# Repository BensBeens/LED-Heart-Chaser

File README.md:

# LED-Heart-Chaser
Little project that I made as a gift for others. It is a LED chaser circuit that would turn on LEDs in a heart shape when plugged into a USB port. 
It uses a NE555 timer and a 4017 counter for the chaser circuit. It is a 4 layer board (signal layers 1 and 4, VCC layer 3, and GND layer 2)
Hand soldered the SMD components on the PCB when I got the board from Oshpark.com (sourced the components from Mouser.com).

Here is the schematic:

Here is the front of the PCB:

Here is the back of the PCB:

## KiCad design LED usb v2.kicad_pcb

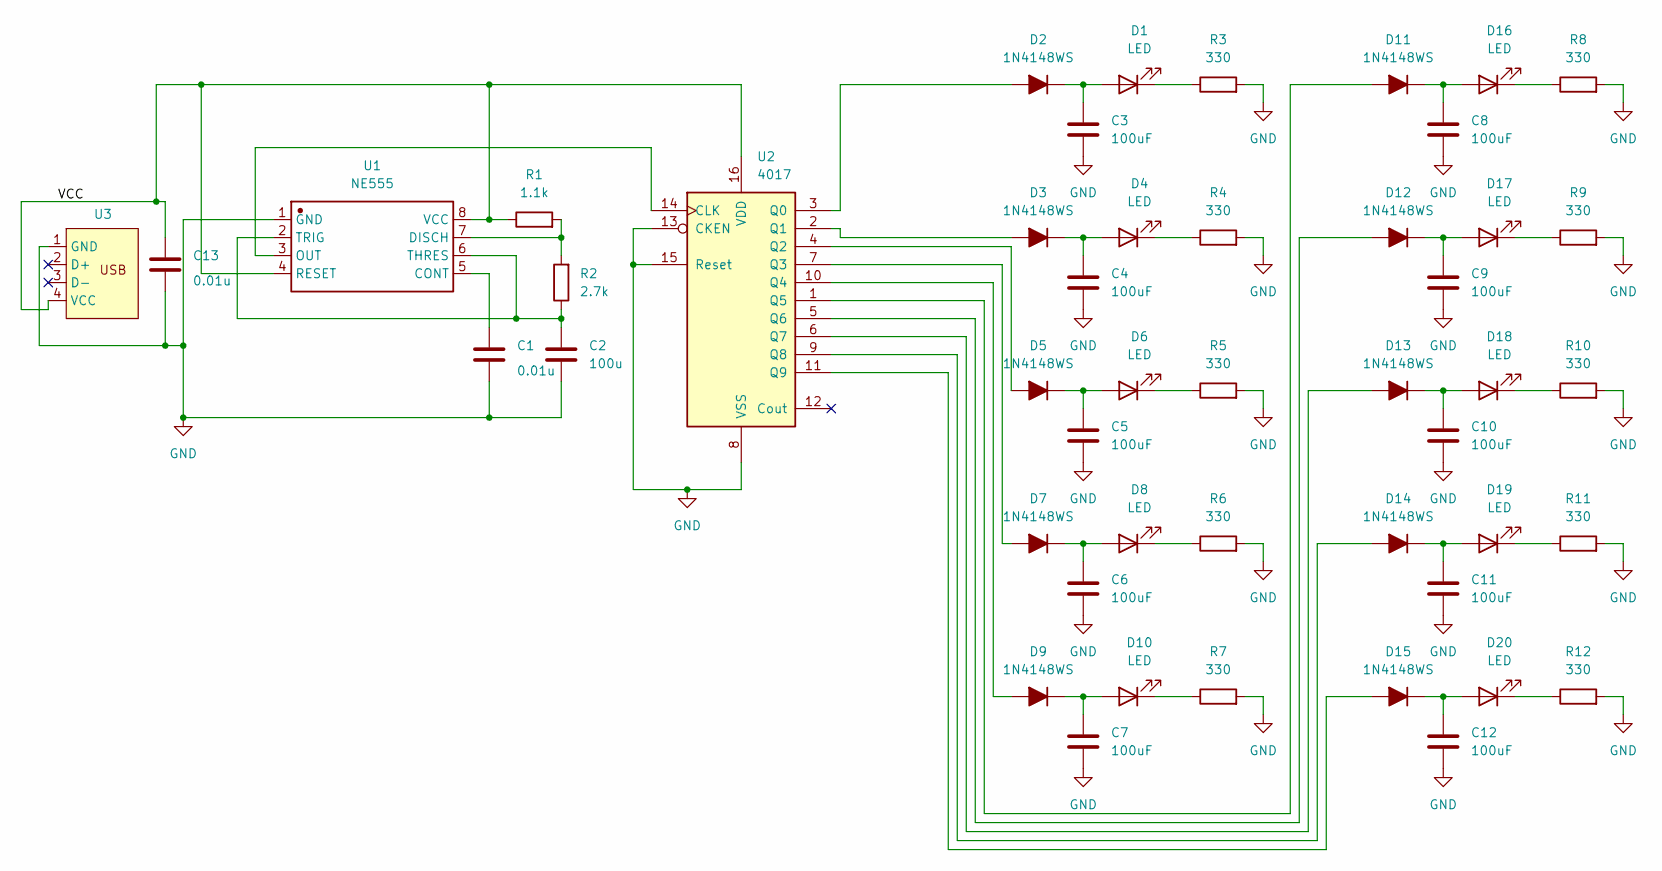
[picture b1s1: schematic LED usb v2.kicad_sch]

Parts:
C1, C13: 0.01u; 0.01uF(10nF)_C0603
C2: 100u; CAP_SMT_C1206
C3, C4, C5, C6, C7, C8, C9, C10, C11, C12: 100uF; CAP_SMT_C1206
D1, D4, D6, D8, D10, D16, D17, D18, D19, D20: LED; RED_SMD_LED0603-RD
D2, D3, D5, D7, D9, D11, D12, D13, D14, D15: 1N4148WS; Diode_SOD-323_L1.7-W1.3-LS2.7-RD
R1: 1.1k; R0603
R2: 2.7k; R0603
R3, R4, R5, R6, R7, R8, R9, R10, R11, R12: 330; R0603
U1: NE555; NE555DR_SOIC-8_L4.9-W3.9-P1.27-LS6.0-BL; Manufacturer Part NE555
U2: 4017; CD4017BM96G4_SOIC-16_L9.9-W3.9-P1.27-LS6.0-BL
U3: USB_Connector_PCB

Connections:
/VCC: C13.2, R1.1, U1.4 (RESET), U1.8 (VCC), U2.16 (VDD), U3.4 (VCC)
GND: C1.1, C2.1, C3.2, C4.2, C5.2, C6.2, C7.2, C8.2, C9.2, C10.2, C11.2, C12.2, C13.1, R3.2, R4.2, R5.2, R6.2, R7.2, R8.2, R9.2, R10.2, R11.2, R12.2, U1.1 (GND), U2.8 (VSS), U2.13 (CKEN), U2.15 (Reset), U3.1 (GND)
unnamed: C3.1, D1.2 (A), D2.1 (K)
unnamed: D1.1 (K), R3.1
unnamed: D2.2 (A), U2.3 (Q0)
unnamed: D3.2 (A), U2.2 (Q1)
unnamed: C4.1, D3.1 (K), D4.2 (A)
unnamed: D4.1 (K), R4.1
unnamed: D5.2 (A), U2.4 (Q2)
unnamed: C5.1, D5.1 (K), D6.2 (A)
unnamed: D6.1 (K), R5.1
unnamed: D7.2 (A), U2.7 (Q3)
unnamed: C6.1, D7.1 (K), D8.2 (A)
unnamed: D8.1 (K), R6.1
unnamed: D9.2 (A), U2.10 (Q4)
unnamed: C7.1, D9.1 (K), D10.2 (A)
unnamed: D10.1 (K), R7.1
unnamed: D11.2 (A), U2.1 (Q5)
unnamed: C8.1, D11.1 (K), D16.2 (A)
unnamed: D12.2 (A), U2.5 (Q6)
unnamed: C9.1, D12.1 (K), D17.2 (A)
unnamed: D13.2 (A), U2.6 (Q7)
unnamed: C10.1, D13.1 (K), D18.2 (A)
unnamed: D14.2 (A), U2.9 (Q8)
unnamed: C11.1, D14.1 (K), D19.2 (A)
unnamed: D15.2 (A), U2.11 (Q9)
unnamed: C12.1, D15.1 (K), D20.2 (A)
unnamed: D16.1 (K), R8.1
unnamed: D17.1 (K), R9.1
unnamed: D18.1 (K), R10.1
unnamed: D19.1 (K), R11.1
unnamed: D20.1 (K), R12.1
unnamed: C1.2, U1.5 (CONT)
unnamed: R1.2, R2.2, U1.7 (DISCH)
unnamed: U1.3 (OUT), U2.14 (CLK)
unnamed: C2.2, R2.1, U1.2 (TRIG), U1.6 (THRES)

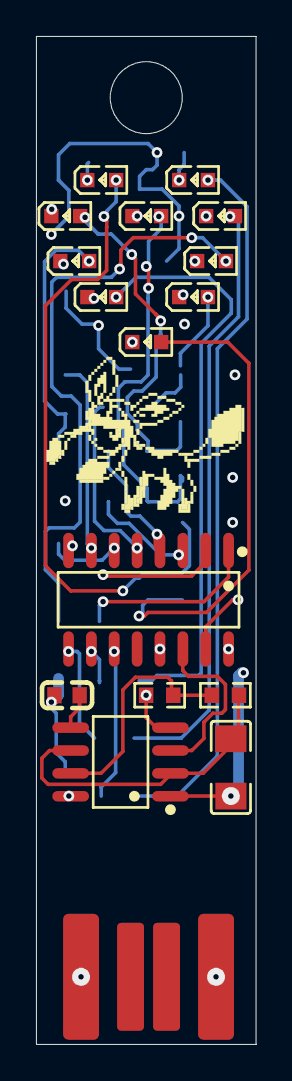
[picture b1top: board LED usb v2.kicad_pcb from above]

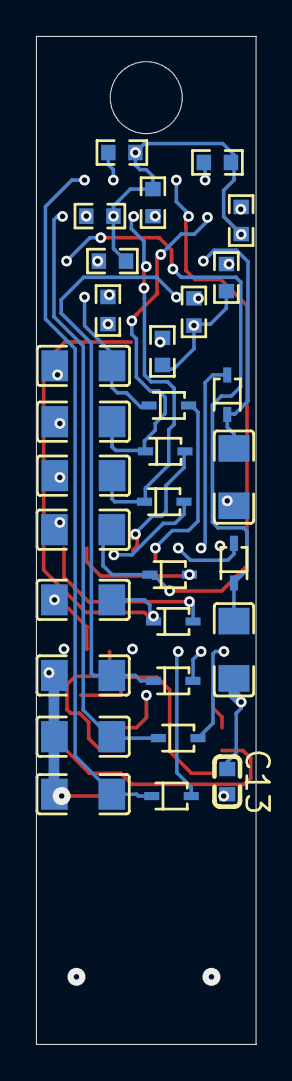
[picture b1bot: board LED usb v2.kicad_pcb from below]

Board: 4 copper layers, 12.2 x 56.0 mm, 48 parts (31 on the bottom side), 36 nets.

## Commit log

2026-01-30 Added the schematic, PCB, and project files
